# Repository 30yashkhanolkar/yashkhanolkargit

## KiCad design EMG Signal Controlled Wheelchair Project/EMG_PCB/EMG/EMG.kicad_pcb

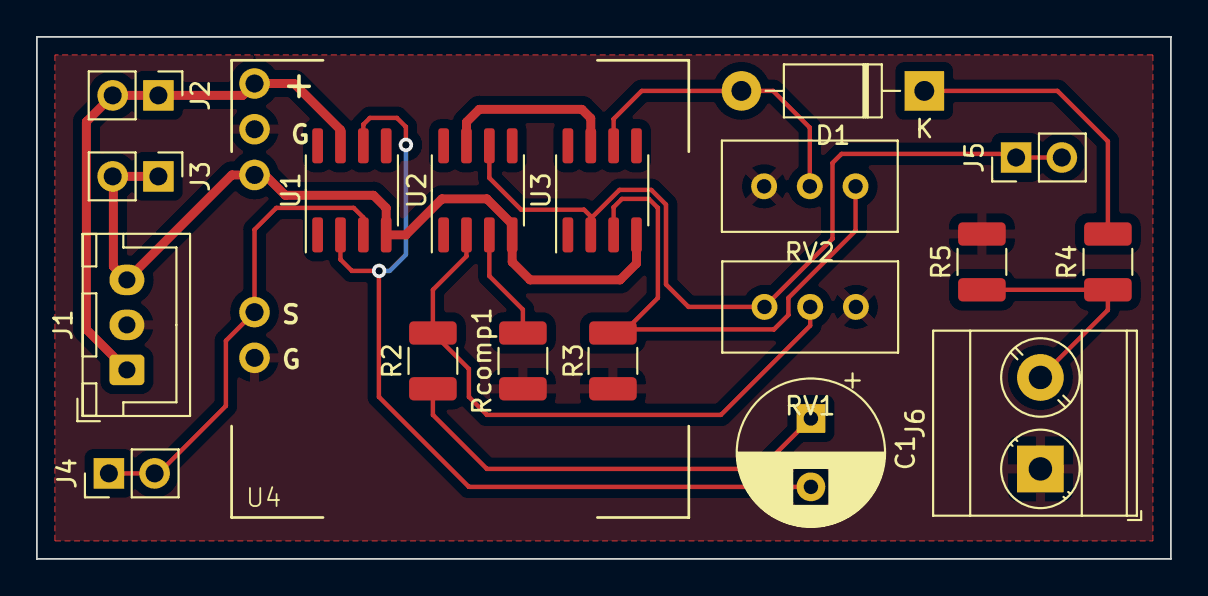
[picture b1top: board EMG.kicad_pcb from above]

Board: 2 copper layers, 63.0 x 29.0 mm, 19 parts (0 on the bottom side), 13 nets.

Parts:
C1: 100u; CP_Radial_D8.0mm_P3.80mm
D1: 1N4007; D_DO-41_SOD81_P10.16mm_Horizontal
J1: Supply; JST_XH_B3B-XH-A_1x03_P2.50mm_Vertical
J2: +Vcc; PinHeader_1x02_P2.54mm_Vertical
J3: -Vcc; PinHeader_1x02_P2.54mm_Vertical
J4: EMG Input; PinHeader_1x02_P2.54mm_Vertical
J5: Amp_Output; PinHeader_1x02_P2.54mm_Vertical
J6: Output; TerminalBlock_Phoenix_MKDS-3-2-5.08_1x02_P5.08mm_Horizontal
R2, R3: 1k; R_1210_3225Metric_Pad1.30x2.65mm_HandSolder
R4, R5: 10k; R_1210_3225Metric_Pad1.30x2.65mm_HandSolder
RV1: Gain; Potentiometer_Bourns_3296W_Vertical
RV2: Threshold; Potentiometer_Bourns_3296W_Vertical
Rcomp1: 820R; R_1210_3225Metric_Pad1.30x2.65mm_HandSolder
U1, U2, U3: OP07; SOIC-8_3.9x4.9mm_P1.27mm
U4: Muscle Sensor V3

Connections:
/Amp_Output: J5.1, J5.2, RV1.3, U2.6, U3.2 (-)
/Buff_Output: C1.2, U1.2 (-), U1.6
/EMG_Input: J4.1, J4.2, U1.3 (+), U4.4 (SIG)
/Output: J6.2, R4.1, R5.1
GND: J1.2, J6.1, R3.2, R5.2, RV1.1, RV2.1, Rcomp1.1, U4.2 (GND), U4.5 (GND)
unnamed: C1.1, R2.1
unnamed: D1.2 (A), RV2.2, U3.6
unnamed: D1.1 (K), R4.2
unnamed: Rcomp1.2, U2.3 (+)
unnamed: R2.2, RV1.2, U2.2 (-)
unnamed: R3.1, RV2.3, U3.3 (+)
VCC: J1.1, J2.1, J2.2, U1.7 (V+), U2.7 (V+), U3.7 (V+), U4.1 (+Vcc)
VEE: J1.3, J3.1, J3.2, U1.4 (V-), U2.4 (V-), U3.4 (V-), U4.3 (-Vcc)

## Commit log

2024-04-14 Create Implementing Extended Kalman Filter (EKF) for State Estimation
2024-04-14 Create Data3
2024-04-14 Create File3
2024-04-14 Create code3
2024-05-11 Create Unscented Kalman Filter
2024-05-11 Create Unscented Kalman Filter(UKF)
2024-05-11 Create Tzt 1
2024-05-11 Create txt 1
2024-05-11 Create txt1
